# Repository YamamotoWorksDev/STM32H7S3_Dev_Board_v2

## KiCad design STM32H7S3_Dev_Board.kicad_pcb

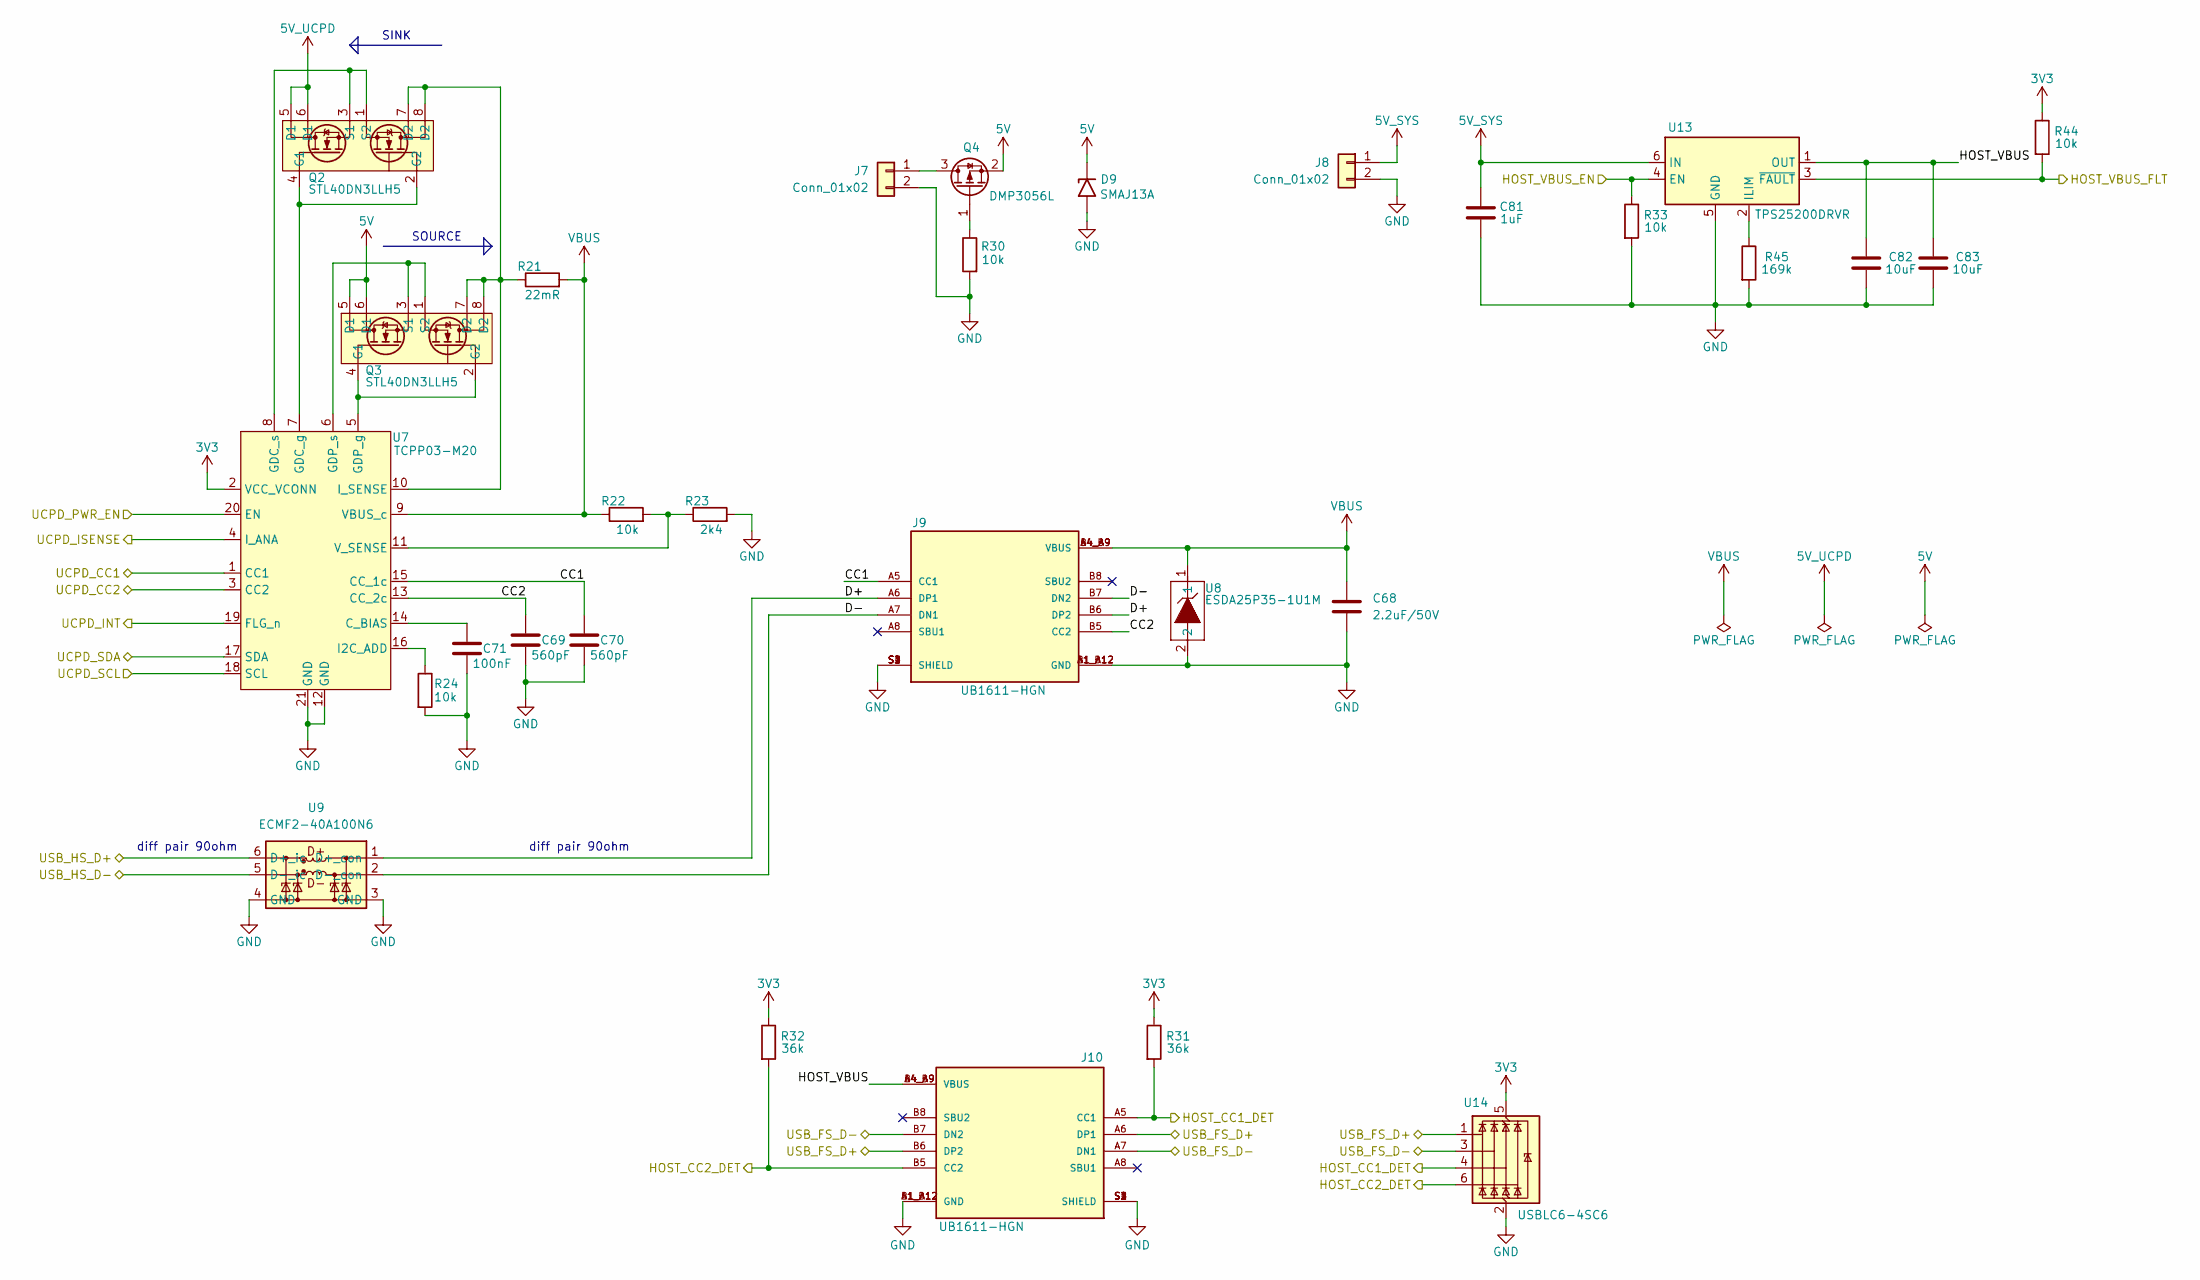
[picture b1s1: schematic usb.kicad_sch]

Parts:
C68: 2.2uF/50V; C_0603_1608Metric
C69, C70: 560pF; C_0201_0603Metric
C71: 100nF; C_0201_0603Metric
C81: 1uF; C_0402_1005Metric
C82, C83: 10uF; C_0402_1005Metric
D9: SMAJ13A; D_SMA
J7: Conn_01x02; JST_XH_B2B-XH-A_1x02_P2.50mm_Vertical
J8: Conn_01x02; JST_PH_B2B-PH-K_1x02_P2.00mm_Vertical
J9: UB1611-HGN; Gangyuan_UB1611-HGN; PARTREV B
J10: UB1611-HGN; Gangyuan_UB1611-HGN
Q2, Q3: STL40DN3LLH5; SON_DN3LLH5_STM
Q4: DMP3056L; SOT-23
R21: 22mR; R_0603_1608Metric
R22, R24, R30, R33, R44: 10k; R_0201_0603Metric
R23: 2k4; R_0201_0603Metric
R31, R32: 36k; R_0201_0603Metric
R45: 169k; R_0201_0603Metric
U7: TCPP03-M20; QFN-20L_4.0X4.0X0.75_STM
U8: ESDA25P35-1U1M; QFN1610_STM
U9: ECMF2-40A100N6; QFN6L_ECMF2_STM
U13: TPS25200DRVR; TI_DRV0006A_WSON-6-1EP_2x2mm_P0.65mm_EP1x1.6mm
U14: USBLC6-4SC6; SOT-23-6

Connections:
3V3: R31.1, R32.1, R44.1, U7.2 (VCC_VCONN), U14.5 (VBUS); also elsewhere on the board
5V: D9.1 (A1), Q3.5 (D1), Q3.6 (D1), Q4.2 (S); also elsewhere on the board
5V_SYS: C81.1, J8.1, U13.6 (IN); also elsewhere on the board
5V_UCPD: Q2.5 (D1), Q2.6 (D1); also elsewhere on the board
/MCU/HOST_CC1_DET: J10.A5 (CC1), R31.2, U14.4 (I/O3); also elsewhere on the board
/MCU/HOST_CC2_DET: J10.B5 (CC2), R32.2, U14.6 (I/O4); also elsewhere on the board
/MCU/HOST_VBUS_EN: R33.1, U13.4 (EN); also elsewhere on the board
/MCU/HOST_VBUS_FLT: R44.2, U13.3 (~FAULT); also elsewhere on the board
/MCU/I2C2_SCL: U7.18 (SCL); also elsewhere on the board
/MCU/I2C2_SDA: U7.17 (SDA); also elsewhere on the board
/MCU/UCPD_CC1: U7.1 (CC1); also elsewhere on the board
/MCU/UCPD_CC2: U7.3 (CC2); also elsewhere on the board
/MCU/UCPD_INT: U7.19 (FLG_n); also elsewhere on the board
/MCU/UCPD_ISENSE: U7.4 (I_ANA); also elsewhere on the board
/MCU/UCPD_PWR_EN: U7.20 (EN); also elsewhere on the board
/MCU/USB_FS_D+: J10.A6 (DP1), J10.B6 (DP2), U14.1 (I/O1); also elsewhere on the board
/MCU/USB_FS_D-: J10.A7 (DN1), J10.B7 (DN2), U14.3 (I/O2); also elsewhere on the board
/MCU/USB_HS_D+: U9.6 (D+_ic); also elsewhere on the board
/MCU/USB_HS_D-: U9.5 (D-_ic); also elsewhere on the board
/USB/CC1: C70.1, J9.A5 (CC1), U7.15 (CC_1c)
/USB/CC2: C69.1, J9.B5 (CC2), U7.13 (CC_2c)
/USB/D+: J9.A6 (DP1), J9.B6 (DP2), U9.1 (D+_con)
/USB/D-: J9.A7 (DN1), J9.B7 (DN2), U9.2 (D-_con)
/USB/HOST_VBUS: C82.1, C83.1, J10.A4_B9 (VBUS), J10.B4_A9 (VBUS), U13.1 (OUT)
GND: C68.2, C69.2, C70.2, C71.2, C81.2, C82.2, C83.2, D9.2 (A2), J7.2, J8.2, J9.A1_B12 (GND), J9.B1_A12 (GND), J9.S1 (SHIELD), J9.S2 (SHIELD), J9.S3 (SHIELD), J9.S4 (SHIELD), J10.A1_B12 (GND), J10.B1_A12 (GND), J10.S1 (SHIELD), J10.S2 (SHIELD), J10.S3 (SHIELD), J10.S4 (SHIELD), R23.2, R24.2, R30.2, R33.2, R45.2, U7.12 (GND), U7.21 (GND), U8.2, U9.3 (GND), U9.4 (GND), U13.5 (GND), U13.7 (GND), U14.2 (GND); also elsewhere on the board
unnamed: J7.1, Q4.3 (D)
unnamed: Q2.2 (G2), Q2.4 (G1), U7.7 (GDC_g)
unnamed: Q2.1 (S2), Q2.3 (S1), U7.8 (GDC_s)
unnamed: Q3.2 (G2), Q3.4 (G1), U7.5 (GDP_g)
unnamed: Q3.1 (S2), Q3.3 (S1), U7.6 (GDP_s)
unnamed: Q4.1 (G), R30.1
unnamed: C71.1, U7.14 (C_BIAS)
unnamed: R24.1, U7.16 (I2C_ADD)
unnamed: Q2.7 (D2), Q2.8 (D2), Q3.7 (D2), Q3.8 (D2), R21.1, U7.10 (I_SENSE)
unnamed: R22.2, R23.1, U7.11 (V_SENSE)
unnamed: R45.1, U13.2 (ILIM)
VBUS: C68.1, J9.A4_B9 (VBUS), J9.B4_A9 (VBUS), R21.2, R22.1, U7.9 (VBUS_c), U8.1

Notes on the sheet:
SOURCE
diff pair 90ohm
SINK

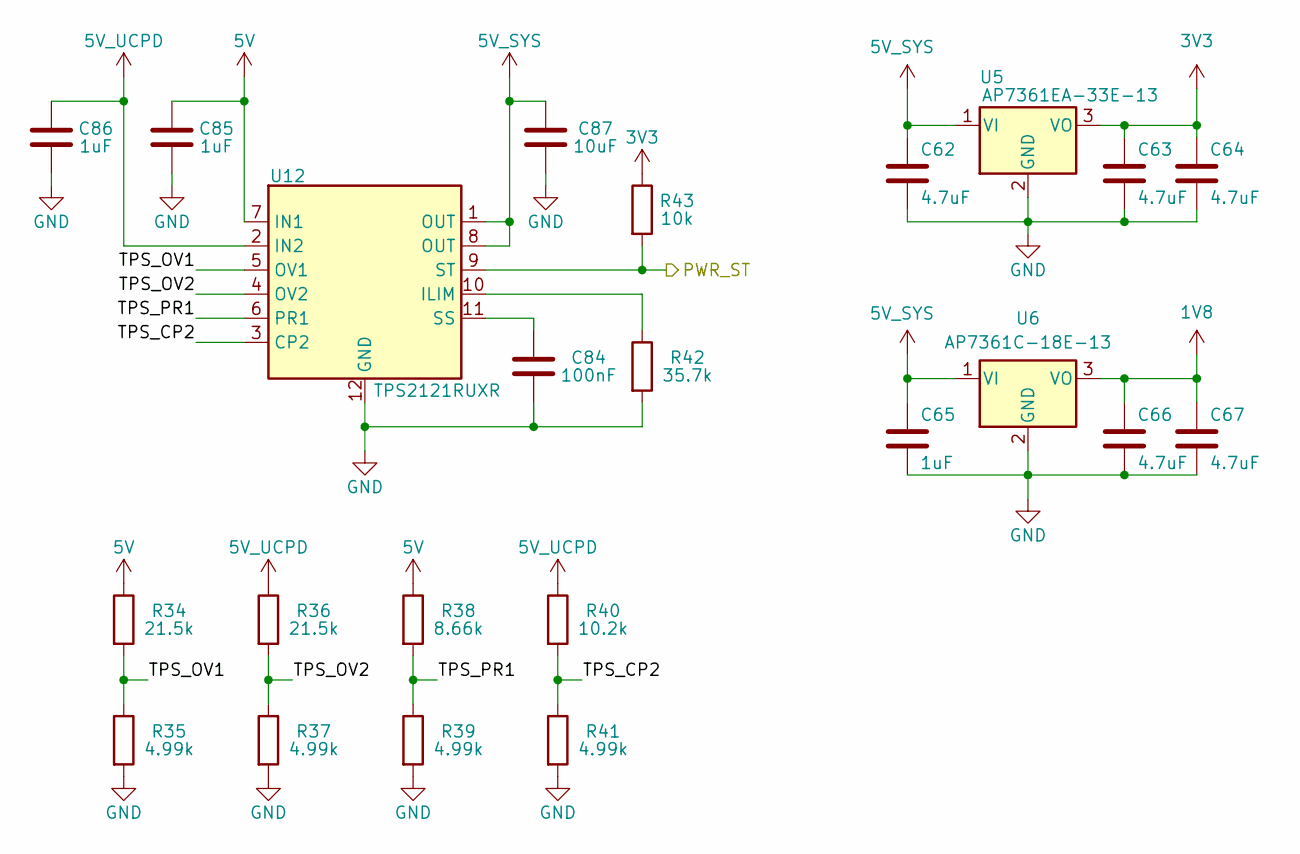
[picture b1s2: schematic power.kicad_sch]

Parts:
C62, C63, C64, C66, C67: 4.7uF; C_0603_1608Metric
C65: 1uF; C_0603_1608Metric
C84: 100nF; C_0201_0603Metric
C85, C86: 1uF; C_0402_1005Metric
C87: 10uF; C_0402_1005Metric
R34, R36: 21.5k; R_0201_0603Metric
R35, R37, R39, R41: 4.99k; R_0201_0603Metric
R38: 8.66k; R_0201_0603Metric
R40: 10.2k; R_0201_0603Metric
R42: 35.7k; R_0201_0603Metric
R43: 10k; R_0201_0603Metric
U5: AP7361EA-33E-13; SOT-223-3_TabPin2
U6: AP7361C-18E-13; SOT-223-3_TabPin2
U12: TPS2121RUXR; TI_RUX0012A_VQFN-HR-12_2x2.5mm_P0.5mm

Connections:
1V8: C66.1, C67.1, U6.3 (VO); also elsewhere on the board
3V3: C63.1, C64.1, R43.1, U5.3 (VO); also elsewhere on the board
5V: C85.1, R34.1, R38.1, U12.7 (IN1); also elsewhere on the board
5V_SYS: C62.1, C65.1, C87.1, U5.1 (VI), U6.1 (VI), U12.1 (OUT), U12.8 (OUT); also elsewhere on the board
5V_UCPD: C86.1, R36.1, R40.1, U12.2 (IN2); also elsewhere on the board
/MCU/PWR_ST: R43.2, U12.9 (ST); also elsewhere on the board
/Power/TPS_CP2: R40.2, R41.1, U12.3 (CP2)
/Power/TPS_OV1: R34.2, R35.1, U12.5 (OV1)
/Power/TPS_OV2: R36.2, R37.1, U12.4 (OV2)
/Power/TPS_PR1: R38.2, R39.1, U12.6 (PR1)
GND: C62.2, C63.2, C64.2, C65.2, C66.2, C67.2, C84.2, C85.2, C86.2, C87.2, R35.2, R37.2, R39.2, R41.2, R42.2, U5.2 (GND), U6.2 (GND), U12.12 (GND); also elsewhere on the board
unnamed: R42.1, U12.10 (ILIM)
unnamed: C84.1, U12.11 (SS)

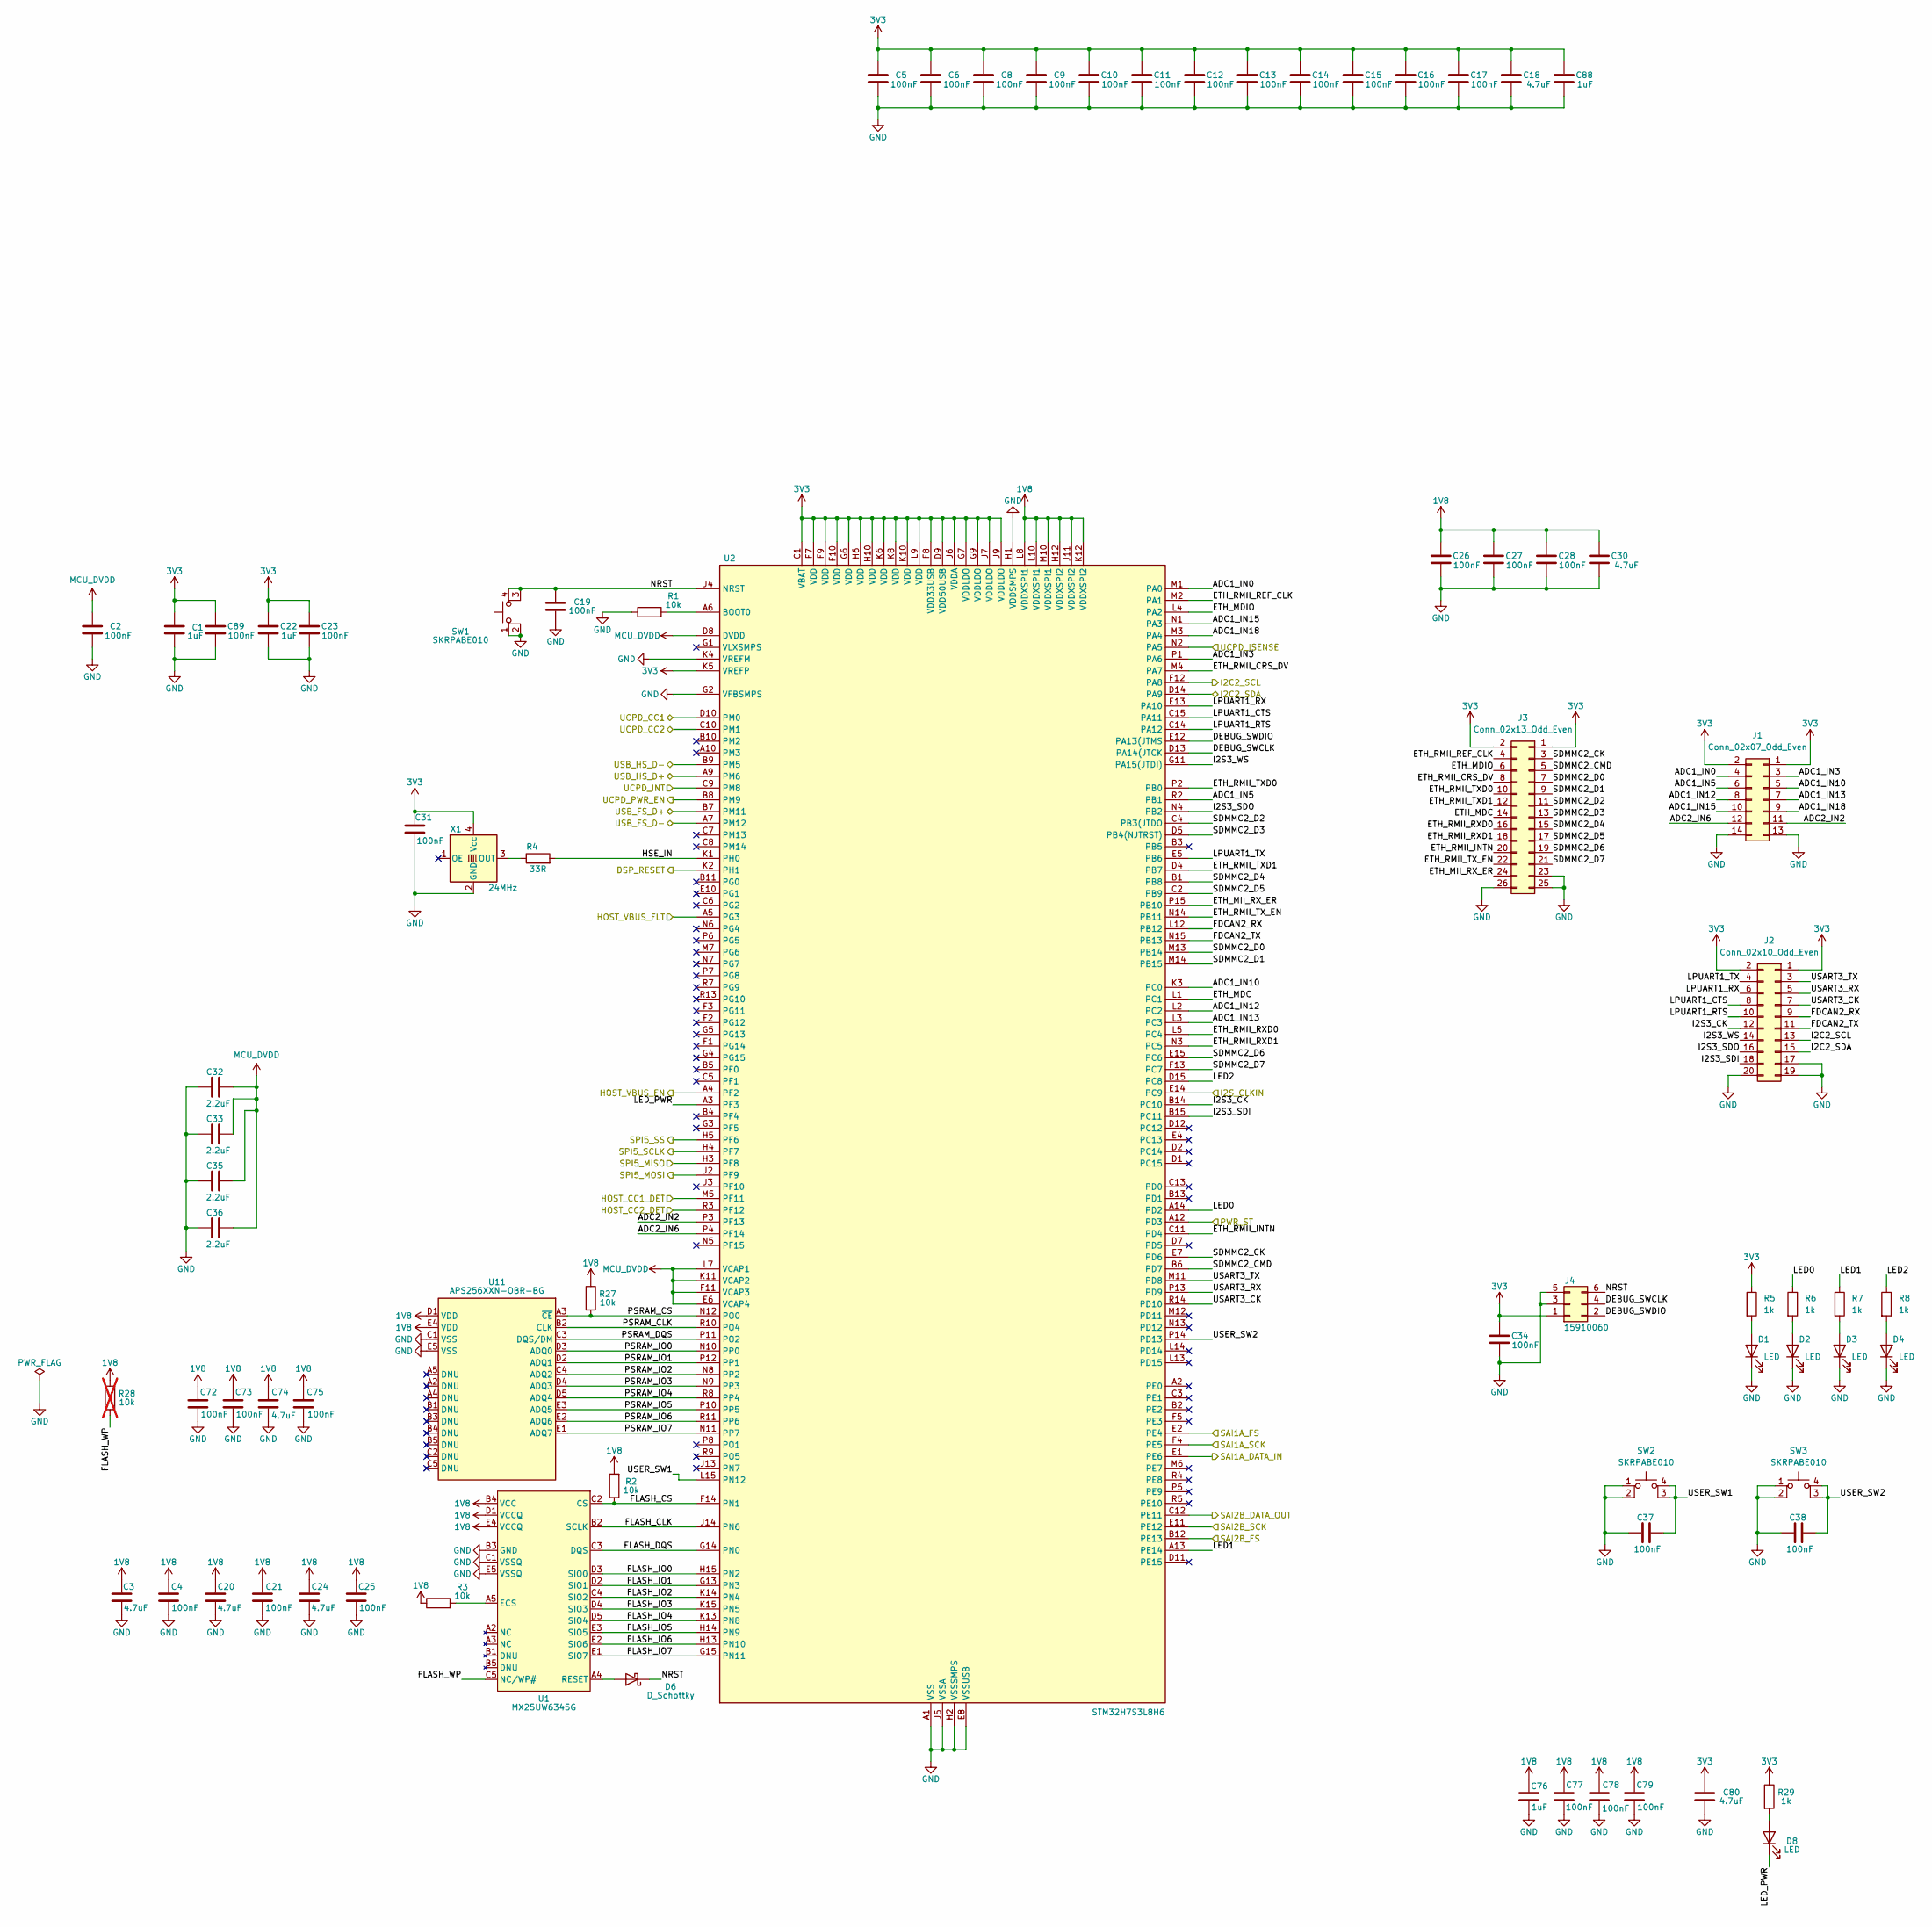
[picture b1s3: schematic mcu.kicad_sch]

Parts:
C1, C22, C76, C88: 1uF; C_0402_1005Metric
C2, C5, C6, C8, C9, C10, C11, C12, C13, C14, C15, C16, C17, C19, C23, C26, C27, C28, C31, C34, C37, C38, C72, C73, C75, C77, C78, C79, C89: 100nF; C_0201_0603Metric
C3, C18, C20, C24, C30, C74, C80: 4.7uF; C_0402_1005Metric
C4, C21, C25: 100nF; C_0402_1005Metric
C32, C33, C35, C36: 2.2uF; C_0402_1005Metric
D1, D2, D3, D4, D8: LED; LED_0603_1608Metric
D6: D_Schottky; D_SOD-523
J1: Conn_02x07_Odd_Even; PinSocket_2x07_P2.54mm_Vertical
J2: Conn_02x10_Odd_Even; PinSocket_2x10_P2.54mm_Vertical
J3: Conn_02x13_Odd_Even; PinSocket_2x13_P2.54mm_Vertical
J4: 15910060; PinHeader_2x03_P2.54mm_Vertical
R1, R2, R3, R27: 10k; R_0201_0603Metric
R4: 33R; R_0201_0603Metric
R5, R6, R7, R8, R29: 1k; R_0201_0603Metric
R28: 10k; R_0201_0603Metric; not fitted
SW1, SW2, SW3: SKRPABE010
U1: MX25UW6345G; BGA24C100P5X5_800X600X120
U2: STM32H7S3L8H6; ST_TFBGA-225_13x13mm_Layout15x15_P0.8mm
U11: APS256XXN-OBR-BG; BGA24C100P5X5_800X600X120
X1: 24MHz; Oscillator_SMD_SeikoEpson_SG210-4Pin_2.5x2.0mm

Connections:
1V8: C3.2, C4.2, C20.2, C21.2, C24.2, C25.2, C26.2, C27.2, C28.2, C30.2, C72.1, C73.1, C74.1, C75.1, C76.1, C77.1, C78.1, C79.1, R2.2, R3.1, R27.1, R28.1, U1.B4 (VCC), U1.D1 (VCCQ), U1.E4 (VCCQ), U2.H12 (VDDXSPI2), U2.J11 (VDDXSPI2), U2.K12 (VDDXSPI2), U2.L8 (VDDXSPI1), U2.L10 (VDDXSPI1), U2.M10 (VDDXSPI1), U11.D1 (VDD), U11.E4 (VDD); also elsewhere on the board
3V3: C1.2, C5.2, C6.2, C8.2, C9.2, C10.2, C11.2, C12.2, C13.2, C14.2, C15.2, C16.2, C17.2, C18.2, C22.2, C23.2, C31.2, C34.2, C80.1, C88.2, C89.2, J1.1, J1.2, J2.1, J2.2, J3.1, J3.2, J4.1, R5.1, R29.1, U2.C1 (VBAT), U2.D9 (VDD50USB), U2.F7 (VDD), U2.F8 (VDD33USB), U2.F9 (VDD), U2.F10 (VDD), U2.G6 (VDD), U2.G7 (VDDLDO), U2.G9 (VDDLDO), U2.H6 (VDD), U2.H10 (VDD), U2.J6 (VDDA), U2.J7 (VDDLDO), U2.J9 (VDDLDO), U2.K5 (VREFP), U2.K6 (VDD), U2.K8 (VDD), U2.K10 (VDD), U2.L9 (VDD), X1.4 (Vcc); also elsewhere on the board
/DSP/CLKOUT: U2.E14 (PC9); also elsewhere on the board
/DSP/DSP_BCLK_IN0: U2.E11 (PE12); also elsewhere on the board
/DSP/DSP_BCLK_OUT0: U2.F4 (PE5); also elsewhere on the board
/DSP/DSP_LRCLK_IN0: U2.B12 (PE13); also elsewhere on the board
/DSP/DSP_LRCLK_OUT0: U2.E2 (PE4); also elsewhere on the board
/DSP/DSP_RESET: U2.K2 (PH1); also elsewhere on the board
/DSP/DSP_SDATA_IN0: U2.C12 (PE11); also elsewhere on the board
/DSP/DSP_SDATA_OUT0: U2.E1 (PE6); also elsewhere on the board
/DSP/USBi_MISO: U2.H3 (PF8); also elsewhere on the board
/DSP/USBi_MOSI: U2.J2 (PF9); also elsewhere on the board
/DSP/USBi_SCLK: U2.H4 (PF7); also elsewhere on the board
/DSP/USBi_SS: U2.H5 (PF6); also elsewhere on the board
/MCU/ADC1_IN0: J1.4, U2.M1 (PA0)
/MCU/ADC1_IN3: J1.3, U2.P1 (PA6)
/MCU/ADC1_IN5: J1.6, U2.R2 (PB1)
/MCU/ADC1_IN10: J1.5, U2.K3 (PC0)
/MCU/ADC1_IN12: J1.8, U2.L2 (PC2)
/MCU/ADC1_IN13: J1.7, U2.L3 (PC3)
/MCU/ADC1_IN15: J1.10, U2.N1 (PA3)
/MCU/ADC1_IN18: J1.9, U2.M3 (PA4)
/MCU/ADC2_IN2: J1.11, U2.P3 (PF13)
/MCU/ADC2_IN6: J1.12, U2.P4 (PF14)
/MCU/DEBUG_SWCLK: J4.4, U2.D13 (PA14(JTCK)
/MCU/DEBUG_SWDIO: J4.2, U2.E12 (PA13(JTMS)
/MCU/ETH_MDC: J3.14, U2.L1 (PC1)
/MCU/ETH_MDIO: J3.6, U2.L4 (PA2)
/MCU/ETH_MII_RX_ER: J3.24, U2.P15 (PB10)
/MCU/ETH_RMII_CRS_DV: J3.8, U2.M4 (PA7)
/MCU/ETH_RMII_INTN: J3.20, U2.C11 (PD4)
/MCU/ETH_RMII_REF_CLK: J3.4, U2.M2 (PA1)
/MCU/ETH_RMII_RXD0: J3.16, U2.L5 (PC4)
/MCU/ETH_RMII_RXD1: J3.18, U2.N3 (PC5)
/MCU/ETH_RMII_TXD0: J3.10, U2.P2 (PB0)
/MCU/ETH_RMII_TXD1: J3.12, U2.D4 (PB7)
/MCU/ETH_RMII_TX_EN: J3.22, U2.N14 (PB11)
/MCU/FDCAN2_RX: J2.9, U2.L12 (PB12)
/MCU/FDCAN2_TX: J2.11, U2.N15 (PB13)
/MCU/FLASH_CLK: U1.B2 (SCLK), U2.J14 (PN6)
/MCU/FLASH_CS: R2.1, U1.C2 (CS), U2.F14 (PN1)
/MCU/FLASH_DQS: U1.C3 (DQS), U2.G14 (PN0)
/MCU/FLASH_IO0: U1.D3 (SIO0), U2.H15 (PN2)
/MCU/FLASH_IO1: U1.D2 (SIO1), U2.G13 (PN3)
/MCU/FLASH_IO2: U1.C4 (SIO2), U2.K14 (PN4)
/MCU/FLASH_IO3: U1.D4 (SIO3), U2.K15 (PN5)
/MCU/FLASH_IO4: U1.D5 (SIO4), U2.K13 (PN8)
/MCU/FLASH_IO5: U1.E3 (SIO5), U2.H14 (PN9)
/MCU/FLASH_IO6: U1.E2 (SIO6), U2.H13 (PN10)
/MCU/FLASH_IO7: U1.E1 (SIO7), U2.G15 (PN11)
/MCU/FLASH_WP: R28.2, U1.C5 (NC/WP#)
/MCU/HOST_CC1_DET: U2.M5 (PF11); also elsewhere on the board
/MCU/HOST_CC2_DET: U2.R3 (PF12); also elsewhere on the board
/MCU/HOST_VBUS_EN: U2.A4 (PF2); also elsewhere on the board
/MCU/HOST_VBUS_FLT: U2.A5 (PG3); also elsewhere on the board
/MCU/HSE_IN: R4.2, U2.K1 (PH0)
/MCU/I2C2_SCL: J2.13, U2.F12 (PA8); also elsewhere on the board
/MCU/I2C2_SDA: J2.15, U2.D14 (PA9); also elsewhere on the board
/MCU/I2S3_CK: J2.12, U2.B14 (PC10)
/MCU/I2S3_SDI: J2.18, U2.B15 (PC11)
/MCU/I2S3_SDO: J2.16, U2.N4 (PB2)
/MCU/I2S3_WS: J2.14, U2.G11 (PA15(JTDI))
/MCU/LED0: R6.1, U2.A14 (PD2)
/MCU/LED1: R7.1, U2.A13 (PE14)
/MCU/LED2: R8.1, U2.D15 (PC8)
/MCU/LED_PWR: D8.1 (K), U2.A3 (PF3)
/MCU/LPUART1_CTS: J2.8, U2.C15 (PA11)
/MCU/LPUART1_RTS: J2.10, U2.C14 (PA12)
/MCU/LPUART1_RX: J2.6, U2.E13 (PA10)
/MCU/LPUART1_TX: J2.4, U2.E5 (PB6)
/MCU/NRST: C19.2, D6.1 (K), J4.6, SW1.3 (K), SW1.4 (A), U2.J4 (NRST)
/MCU/PSRAM_CLK: U2.R10 (PO4), U11.B2 (CLK)
/MCU/PSRAM_CS: R27.2, U2.N12 (PO0), U11.A3 (~CE)
/MCU/PSRAM_DQS: U2.P11 (PO2), U11.C3 (DQS/DM)
/MCU/PSRAM_IO0: U2.N10 (PP0), U11.D3 (ADQ0)
/MCU/PSRAM_IO1: U2.P12 (PP1), U11.D2 (ADQ1)
/MCU/PSRAM_IO2: U2.N8 (PP2), U11.C4 (ADQ2)
/MCU/PSRAM_IO3: U2.N9 (PP3), U11.D4 (ADQ3)
/MCU/PSRAM_IO4: U2.R8 (PP4), U11.D5 (ADQ4)
/MCU/PSRAM_IO5: U2.P10 (PP5), U11.E3 (ADQ5)
/MCU/PSRAM_IO6: U2.R11 (PP6), U11.E2 (ADQ6)
/MCU/PSRAM_IO7: U2.N11 (PP7), U11.E1 (ADQ7)
/MCU/PWR_ST: U2.A12 (PD3); also elsewhere on the board
/MCU/SDMMC2_CK: J3.3, U2.E7 (PD6)
/MCU/SDMMC2_CMD: J3.5, U2.B6 (PD7)
/MCU/SDMMC2_D0: J3.7, U2.M13 (PB14)
/MCU/SDMMC2_D1: J3.9, U2.M14 (PB15)
/MCU/SDMMC2_D2: J3.11, U2.C4 (PB3(JTDO)
/MCU/SDMMC2_D3: J3.13, U2.D5 (PB4(NJTRST))
/MCU/SDMMC2_D4: J3.15, U2.B1 (PB8)
/MCU/SDMMC2_D5: J3.17, U2.C2 (PB9)
/MCU/SDMMC2_D6: J3.19, U2.E15 (PC6)
/MCU/SDMMC2_D7: J3.21, U2.F13 (PC7)
/MCU/UCPD_CC1: U2.D10 (PM0); also elsewhere on the board
/MCU/UCPD_CC2: U2.C10 (PM1); also elsewhere on the board
/MCU/UCPD_INT: U2.C9 (PM8); also elsewhere on the board
/MCU/UCPD_ISENSE: U2.N2 (PA5); also elsewhere on the board
/MCU/UCPD_PWR_EN: U2.B8 (PM9); also elsewhere on the board
/MCU/USART3_CK: J2.7, U2.R14 (PD10)
/MCU/USART3_RX: J2.5, U2.P13 (PD9)
/MCU/USART3_TX: J2.3, U2.M11 (PD8)
/MCU/USB_FS_D+: U2.B7 (PM11); also elsewhere on the board
/MCU/USB_FS_D-: U2.A7 (PM12); also elsewhere on the board
/MCU/USB_HS_D+: U2.A9 (PM6); also elsewhere on the board
/MCU/USB_HS_D-: U2.B9 (PM5); also elsewhere on the board
/MCU/USER_SW1: C37.2, SW2.3 (K), SW2.4 (A), U2.L15 (PN12)
/MCU/USER_SW2: C38.2, SW3.3 (K), SW3.4 (A), U2.P14 (PD13)
GND: C1.1, C2.1, C3.1, C4.1, C5.1, C6.1, C8.1, C9.1, C10.1, C11.1, C12.1, C13.1, C14.1, C15.1, C16.1, C17.1, C18.1, C19.1, C20.1, C21.1, C22.1, C23.1, C24.1, C25.1, C26.1, C27.1, C28.1, C30.1, C31.1, C32.1, C33.1, C34.1, C35.1, C36.1, C37.1, C38.1, C72.2, C73.2, C74.2, C75.2, C76.2, C77.2, C78.2, C79.2, C80.2, C88.1, C89.1, D1.1 (K), D2.1 (K), D3.1 (K), D4.1 (K), J1.13, J1.14, J2.17, J2.19, J2.20, J3.23, J3.25, J3.26, J4.3, J4.5, R1.1, SW1.1, SW1.2, SW2.1, SW2.2, SW3.1, SW3.2, U1.B3 (GND), U1.C1 (VSSQ), U1.E5 (VSSQ), U2.A1 (VSS), U2.A8 (VSS), U2.A11 (VSS), U2.A15 (VSS), U2.D3 (VSS), U2.D6 (VSS), U2.E3 (VSS), U2.E8 (VSSUSB), U2.E9 (VSS), U2.F6 (VSS), U2.F15 (VSS), U2.G2 (VFBSMPS), U2.G8 (VSS), U2.G10 (VSS), U2.G12 (VSS), U2.H1 (VDDSMPS), U2.H2 (VSSSMPS), U2.H7 (VSS), U2.H8 (VSS), U2.H9 (VSS), U2.H11 (VSS), U2.J1 (VSS), U2.J5 (VSSA), U2.J8 (VSS), U2.J10 (VSS), U2.J12 (VSS), U2.J15 (VSS), U2.K4 (VREFM), U2.K7 (VSS), U2.K9 (VSS), U2.L6 (VSS), U2.L11 (VSS), U2.M8 (VSS), U2.M9 (VSS), U2.M15 (VSS), U2.P9 (VSS), U2.R1 (VSS), U2.R6 (VSS), U2.R12 (VSS), U2.R15 (VSS), U11.C1 (VSS), U11.E5 (VSS), X1.2 (GND); also elsewhere on the board
MCU_DVDD: C2.2, C32.2, C33.2, C35.2, C36.2, U2.D8 (DVDD), U2.E6 (VCAP4), U2.F11 (VCAP3), U2.K11 (VCAP2), U2.L7 (VCAP1)
unnamed: D1.2 (A), R5.2
unnamed: D2.2 (A), R6.2
unnamed: D3.2 (A), R7.2
unnamed: D4.2 (A), R8.2
unnamed: D6.2 (A), U1.A4 (RESET)
unnamed: D8.2 (A), R29.2
unnamed: R3.2, U1.A5 (ECS)
unnamed: R1.2, U2.A6 (BOOT0)
unnamed: R4.1, X1.3 (OUT)

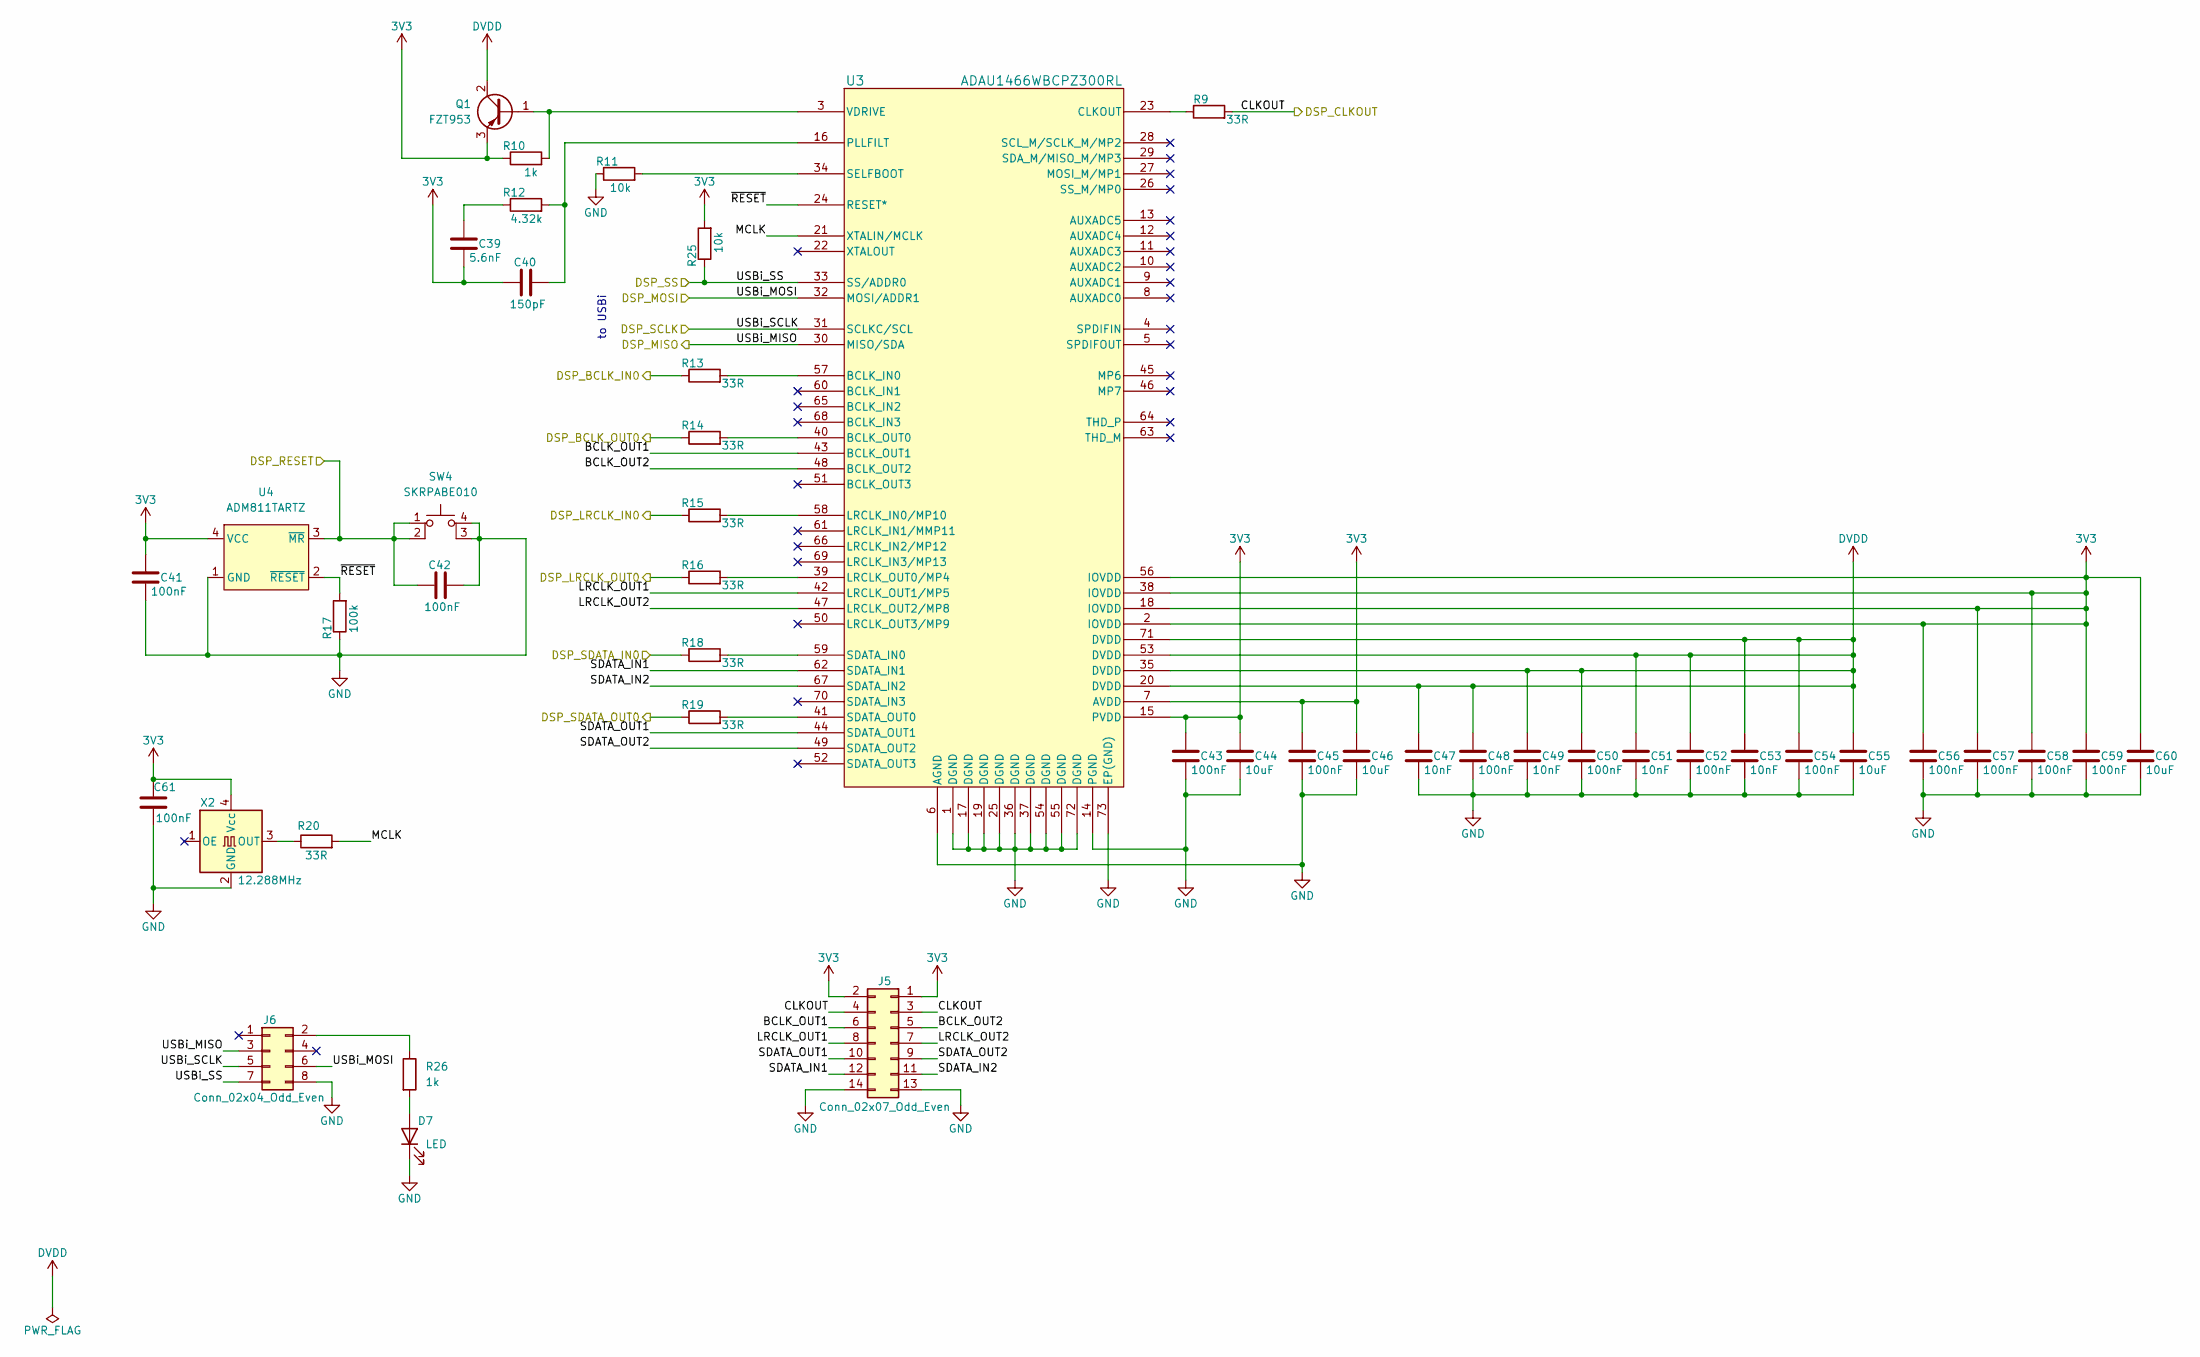
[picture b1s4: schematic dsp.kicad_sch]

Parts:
C39: 5.6nF; C_0201_0603Metric
C40: 150pF; C_0201_0603Metric
C41, C42, C43, C45, C48, C50, C52, C54, C56, C57, C58, C59: 100nF; C_0201_0603Metric
C44, C46, C55, C60: 10uF; C_0402_1005Metric
C47, C49, C51, C53: 10nF; C_0201_0603Metric
C61: 100nF; C_0402_1005Metric
D7: LED; LED_0603_1608Metric
J5: Conn_02x07_Odd_Even; PinSocket_2x07_P2.54mm_Vertical
J6: Conn_02x04_Odd_Even; PinHeader_2x04_P2.54mm_Vertical
Q1: FZT953; SOT-223-3_TabPin2
R9, R13, R14, R15, R16, R18, R19, R20: 33R; R_0201_0603Metric
R10, R26: 1k; R_0201_0603Metric
R11, R25: 10k; R_0201_0603Metric
R12: 4.32k; R_0201_0603Metric
R17: 100k; R_0201_0603Metric
SW4: SKRPABE010
U3: ADAU1466WBCPZ300RL; CP_72_6_ADI_2
U4: ADM811TARTZ; SOT-143
X2: 12.288MHz; Oscillator_SMD_SeikoEpson_SG210-4Pin_2.5x2.0mm

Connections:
3V3: C39.2, C40.1, C41.1, C43.1, C44.1, C45.1, C46.1, C56.1, C57.1, C58.1, C59.1, C60.1, C61.2, J5.1, J5.2, Q1.3 (E), R10.1, R25.2, U3.2 (IOVDD), U3.7 (AVDD), U3.15 (PVDD), U3.18 (IOVDD), U3.38 (IOVDD), U3.56 (IOVDD), U4.4 (VCC), X2.4 (Vcc); also elsewhere on the board
/DSP/BCLK_OUT1: J5.6, U3.43 (BCLK_OUT1)
/DSP/BCLK_OUT2: J5.5, U3.48 (BCLK_OUT2)
/DSP/CLKOUT: J5.3, J5.4, R9.2; also elsewhere on the board
/DSP/DSP_BCLK_IN0: R13.1; also elsewhere on the board
/DSP/DSP_BCLK_OUT0: R14.1; also elsewhere on the board
/DSP/DSP_LRCLK_IN0: R15.1; also elsewhere on the board
/DSP/DSP_LRCLK_OUT0: R16.1; also elsewhere on the board
/DSP/DSP_RESET: C42.1, SW4.1, SW4.2, U4.3 (~MR); also elsewhere on the board
/DSP/DSP_SDATA_IN0: R18.1; also elsewhere on the board
/DSP/DSP_SDATA_OUT0: R19.1; also elsewhere on the board
/DSP/LRCLK_OUT1: J5.8, U3.42 (LRCLK_OUT1/MP5)
/DSP/LRCLK_OUT2: J5.7, U3.47 (LRCLK_OUT2/MP8)
/DSP/MCLK: R20.2, U3.21 (XTALIN/MCLK)
/DSP/SDATA_IN1: J5.12, U3.62 (SDATA_IN1)
/DSP/SDATA_IN2: J5.11, U3.67 (SDATA_IN2)
/DSP/SDATA_OUT1: J5.10, U3.44 (SDATA_OUT1)
/DSP/SDATA_OUT2: J5.9, U3.49 (SDATA_OUT2)
/DSP/USBi_MISO: J6.3, U3.30 (MISO/SDA); also elsewhere on the board
/DSP/USBi_MOSI: J6.6, U3.32 (MOSI/ADDR1); also elsewhere on the board
/DSP/USBi_SCLK: J6.5, U3.31 (SCLKC/SCL); also elsewhere on the board
/DSP/USBi_SS: J6.7, R25.1, U3.33 (SS/ADDR0); also elsewhere on the board
/DSP/~RESET: R17.2, U3.24 (RESET*), U4.2 (~RESET)
DVDD: C47.1, C48.1, C49.1, C50.1, C51.1, C52.1, C53.1, C54.1, C55.1, Q1.2 (C), U3.20 (DVDD), U3.35 (DVDD), U3.53 (DVDD), U3.71 (DVDD)
GND: C41.2, C42.2, C43.2, C44.2, C45.2, C46.2, C47.2, C48.2, C49.2, C50.2, C51.2, C52.2, C53.2, C54.2, C55.2, C56.2, C57.2, C58.2, C59.2, C60.2, C61.1, D7.1 (K), J5.13, J5.14, J6.8, R11.1, R17.1, SW4.3 (K), SW4.4 (A), U3.1 (DGND), U3.6 (AGND), U3.14 (PGND), U3.17 (DGND), U3.19 (DGND), U3.25 (DGND), U3.36 (DGND), U3.37 (DGND), U3.54 (DGND), U3.55 (DGND), U3.72 (DGND), U3.73 (EP(GND)), U4.1 (GND), X2.2 (GND); also elsewhere on the board
unnamed: C39.1, R12.1
unnamed: D7.2 (A), R26.2
unnamed: J6.2, R26.1
unnamed: Q1.1 (B), R10.2, U3.3 (VDRIVE)
unnamed: R13.2, U3.57 (BCLK_IN0)
unnamed: R14.2, U3.40 (BCLK_OUT0)
unnamed: R9.1, U3.23 (CLKOUT)
unnamed: R15.2, U3.58 (LRCLK_IN0/MP10)
unnamed: R16.2, U3.39 (LRCLK_OUT0/MP4)
unnamed: C40.2, R12.2, U3.16 (PLLFILT)
unnamed: R18.2, U3.59 (SDATA_IN0)
unnamed: R19.2, U3.41 (SDATA_OUT0)
unnamed: R11.2, U3.34 (SELFBOOT)
unnamed: R20.1, X2.3 (OUT)

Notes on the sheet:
to USBi
